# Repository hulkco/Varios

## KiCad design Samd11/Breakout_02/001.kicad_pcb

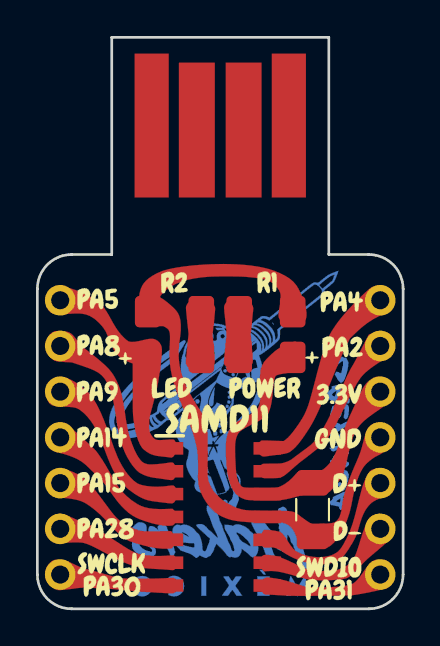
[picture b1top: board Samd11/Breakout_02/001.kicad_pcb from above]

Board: 2 copper layers, 20.3 x 31.8 mm, 12 parts (1 on the bottom side), 16 nets, no tracks yet.

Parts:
C1: 0.1uF; C_1206_3216Metric_Pad1.42x1.75mm_HandSolder
D1: POWER; LED_1206_3216Metric_Pad1.42x1.75mm_HandSolder
D2: LED; LED_1206_3216Metric_Pad1.42x1.75mm_HandSolder
IC2: ATSAMD11C14A-SSUT; SOIC127P600X175-14N
J1: USB_A; USB_A_Plug_PCB
J1#2, J2: Conn_01x07; PinHeader_1x07_P2.54mm_Vertical
R1, R2: 1K; R_1206_3216Metric_Pad1.42x1.75mm_HandSolder
Ref**: Val**; Back_SAMD11
Ref**#2: Val**; Samd21_Breakout_4
U2: Firma; firma_Cu_Mask

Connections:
+3V3: C1.1, D1.2, IC2.12, J2.3
/PA02: IC2.13, J2.2
/PA04: IC2.14, J2.1
/PA05: D2.2, IC2.1, J1#2.1
/PA08: IC2.2, J1#2.2
/PA09: IC2.3, J1#2.3
/PA14: IC2.4, J1#2.4
/PA15: IC2.5, J1#2.5
/PA24: IC2.9, J2.6
/PA25: IC2.10, J2.5
/PA28: IC2.6, J1#2.6
/PA30: IC2.7, J1#2.7
/PA31: IC2.8, J2.7
GND: C1.2, IC2.11, J2.4, R1.2, R2.2
unnamed: D1.1, R1.1
unnamed: D2.1, R2.1

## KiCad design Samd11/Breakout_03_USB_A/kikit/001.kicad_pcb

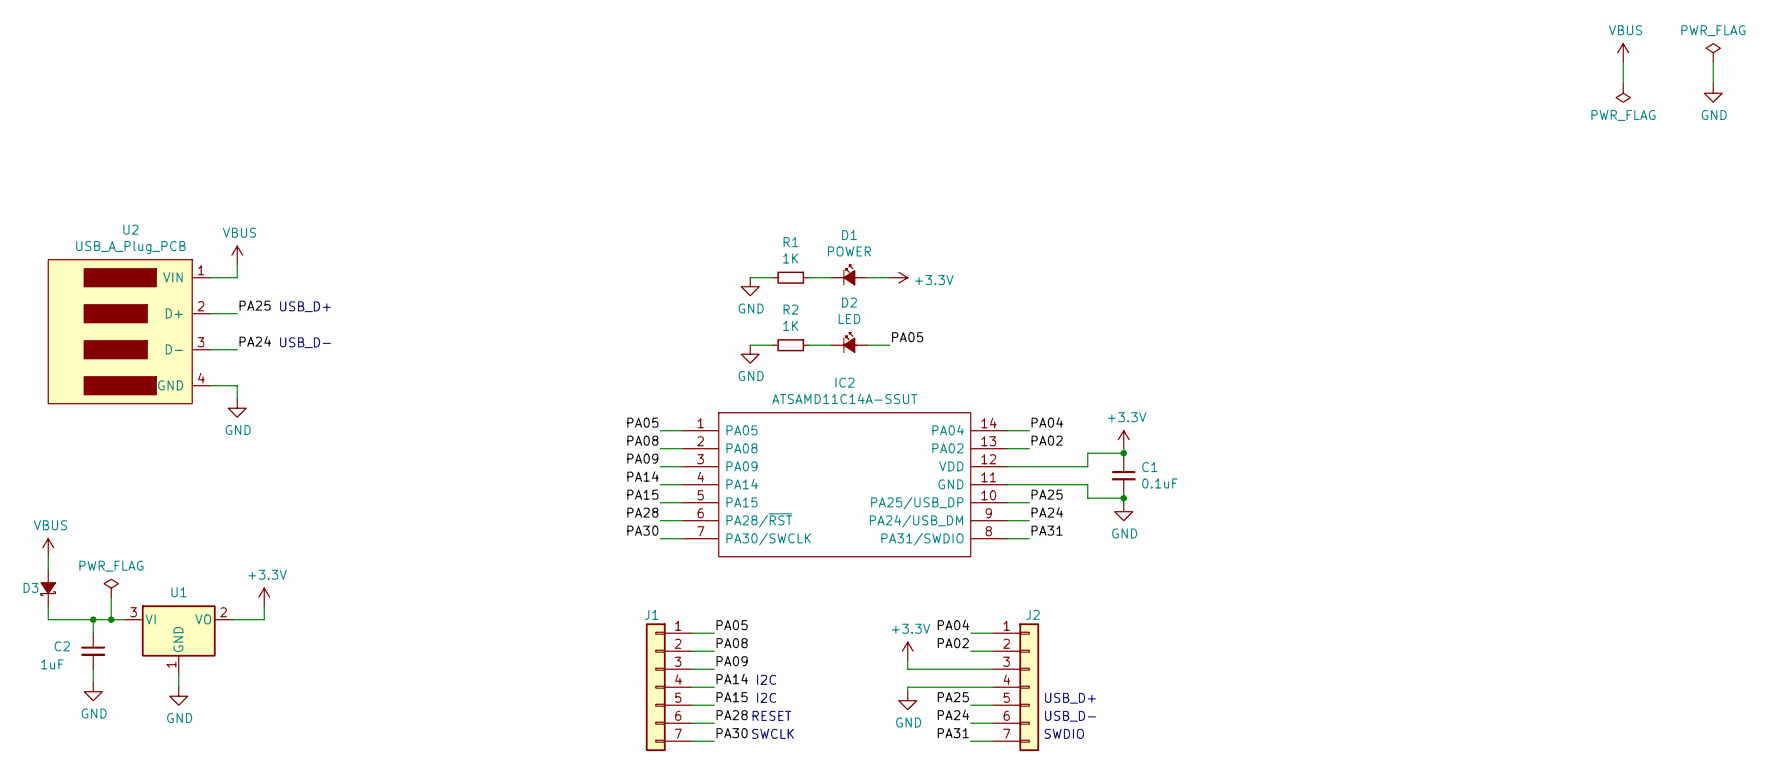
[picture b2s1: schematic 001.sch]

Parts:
C1: 0.1uF; C_1206_3216Metric_Pad1.42x1.75mm_HandSolder
C2: 1uF; C_1206_3216Metric_Pad1.42x1.75mm_HandSolder
D1: POWER; LED_1206_3216Metric_Pad1.42x1.75mm_HandSolder
D2: LED; LED_1206_3216Metric_Pad1.42x1.75mm_HandSolder
D3: MBRA140; D_SOD-123
IC2: ATSAMD11C14A-SSUT; SOIC127P600X175-14N; Mouser Part Number 556-ATSAMD11C14ASSUT
J1, J2: Conn_01x07; PinHeader_1x07_P2.54mm_Vertical
R1, R2: 1K; R_1206_3216Metric_Pad1.42x1.75mm_HandSolder
U1: MCP1700-3302E_SOT23; SOT-23
U2: USB_A_Plug_PCB

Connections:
+3V3: C1.1, D1.2 (A), IC2.12 (VDD), J2.3, U1.2 (VO)
/PA02: IC2.13 (PA02), J2.2
/PA04: IC2.14 (PA04), J2.1
/PA05: D2.2 (A), IC2.1 (PA05), J1.1
/PA08: IC2.2 (PA08), J1.2
/PA09: IC2.3 (PA09), J1.3
/PA14: IC2.4 (PA14), J1.4
/PA15: IC2.5 (PA15), J1.5
/PA24: IC2.9 (PA24/USB_DM), J2.6, U2.3 (D-)
/PA25: IC2.10 (PA25/USB_DP), J2.5, U2.2 (D+)
/PA28: IC2.6 (PA28/~RST), J1.6
/PA30: IC2.7 (PA30/SWCLK), J1.7
/PA31: IC2.8 (PA31/SWDIO), J2.7
GND: C1.2, C2.2, IC2.11 (GND), J2.4, R1.2, R2.2, U1.1 (GND), U2.4 (GND)
unnamed: C2.1, D3.1 (K), U1.3 (VI)
unnamed: D1.1 (K), R1.1
unnamed: D2.1 (K), R2.1
VBUS: D3.2 (A), U2.1 (VIN)

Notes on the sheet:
SWDIO
SWCLK
RESET
I2C
USB_D-
USB_D+

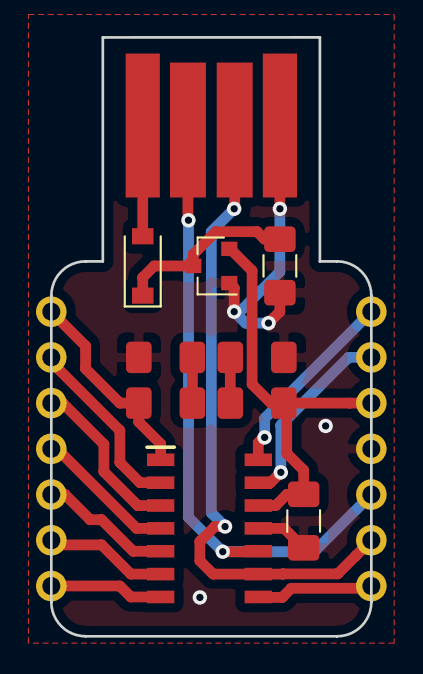
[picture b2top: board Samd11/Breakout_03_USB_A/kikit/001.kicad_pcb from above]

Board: 2 copper layers, 17.8 x 33.3 mm, 12 parts (0 on the bottom side), 18 nets.
